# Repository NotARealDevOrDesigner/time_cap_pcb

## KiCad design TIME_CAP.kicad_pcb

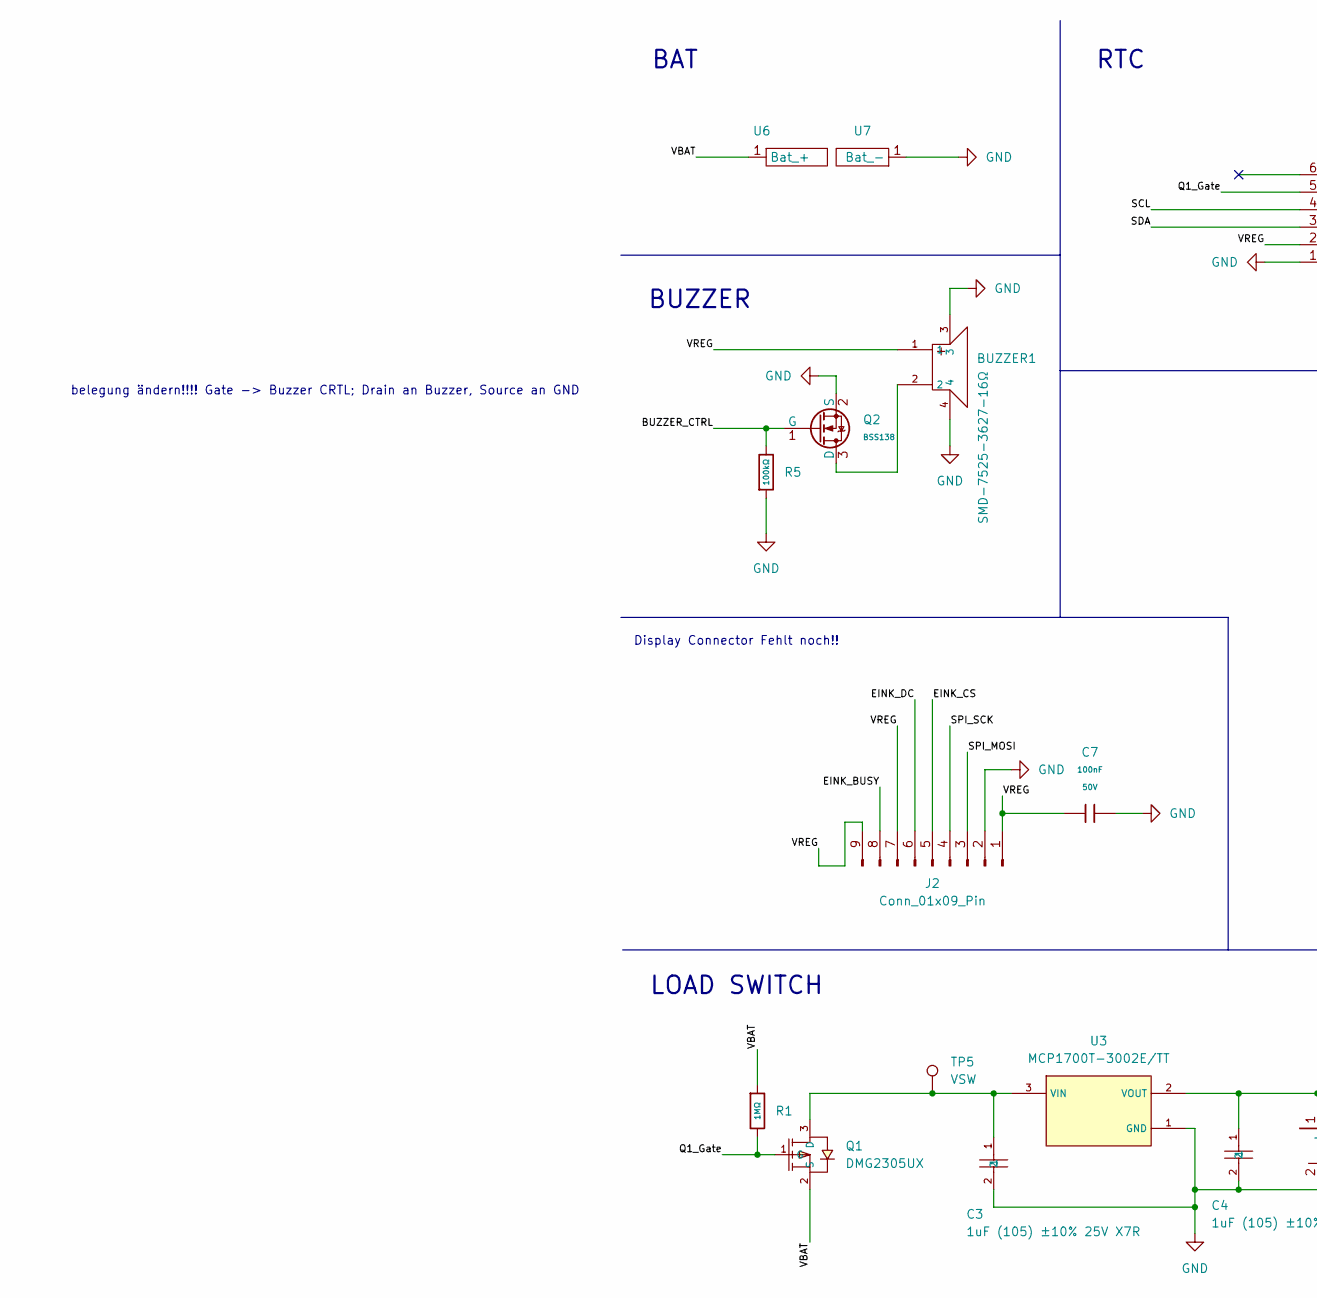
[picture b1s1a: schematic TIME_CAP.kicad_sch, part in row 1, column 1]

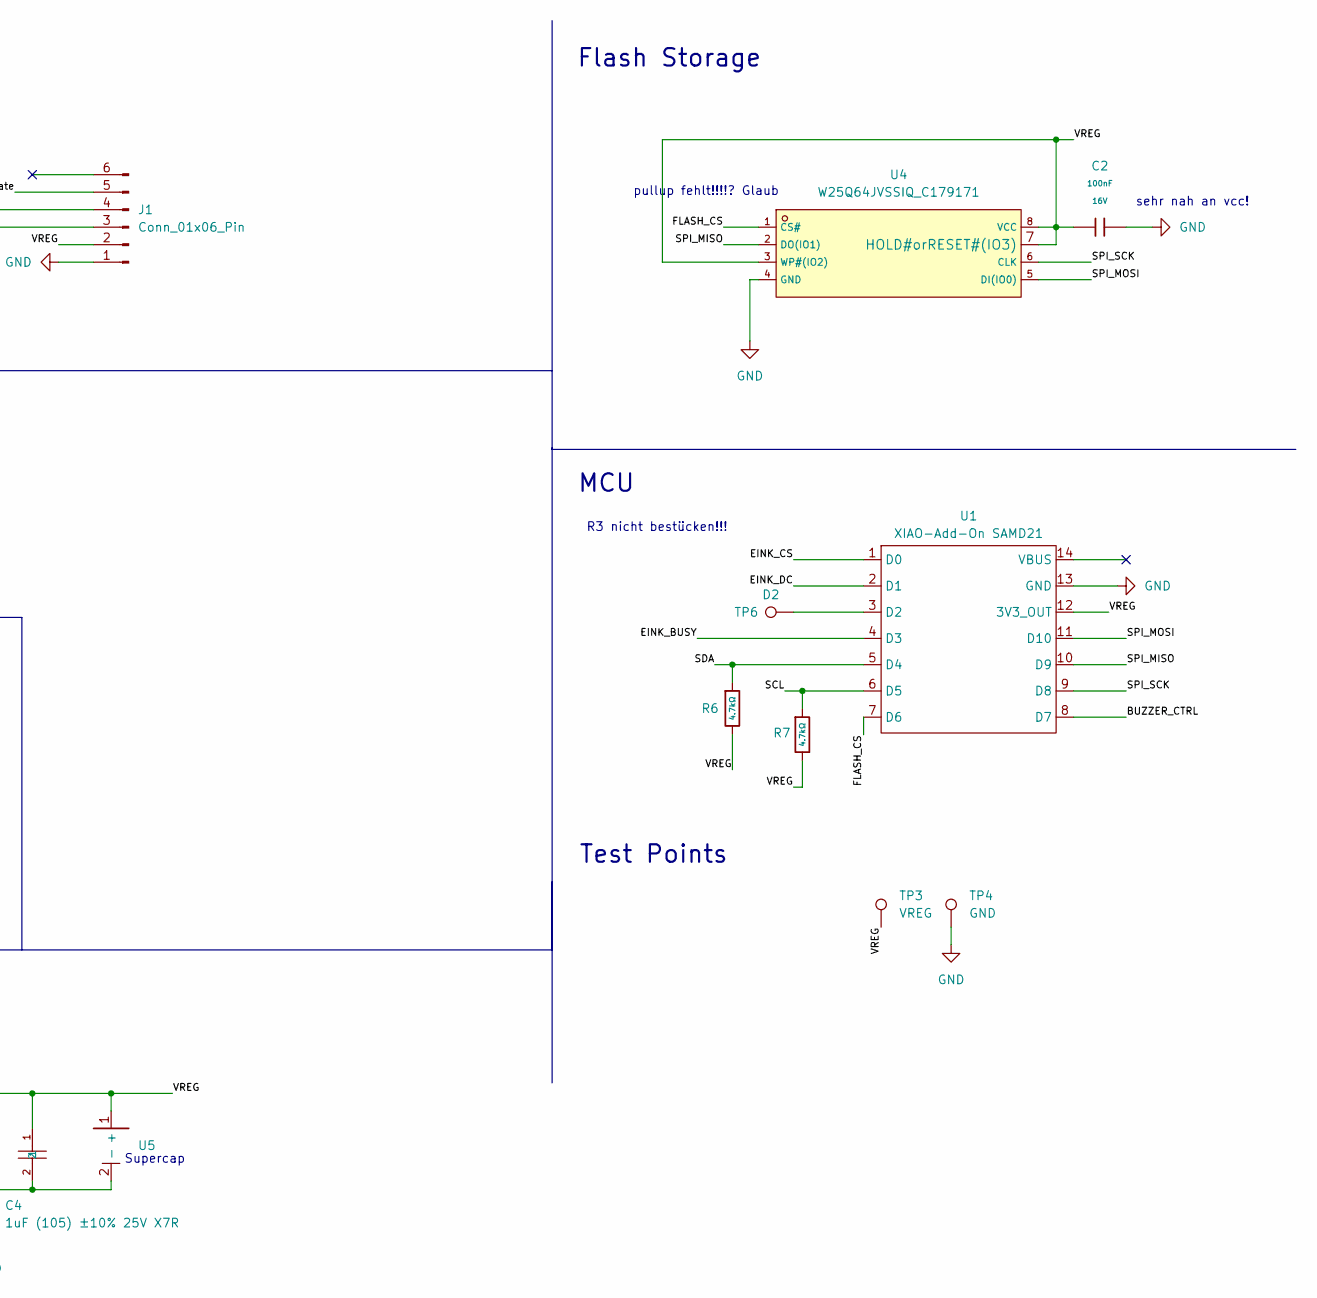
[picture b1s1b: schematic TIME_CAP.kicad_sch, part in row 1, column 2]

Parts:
BUZZER1: SMD-7525-3627-16Ω; C2685546_BUZ-SMD_4P-L7_5-W7_5-BR; LCSC C2685546
C2: 100nF; C_0402; Voltage Rated 16V; Tolerance ±10%; Part CL05B104KO5NNNC; LCSC C1525
C3, C4: 1uF (105) ±10% 25V X7R; C29936_C0603; LCSC C29936
C7: 100nF; C_0603; Voltage Rated 50V; Tolerance ±10%; Part CC0603KRX7R9BB104; LCSC C14663
J1: Conn_01x06_Pin; PinHeader_1x06_P2.54mm_Vertical_SMD_Pin1Right
J2: Conn_01x09_Pin; Display Connector
Q1: DMG2305UX; C2940629_SOT-23-3_L2_9-W1_3-P0_95-LS2_4-BR-1; LCSC C2940629
Q2: BSS138; Q_SOT-23; Part BSS138; LCSC C7420339
R1: 1MΩ; R_0603; Overload Voltage (Max) 75V; Tolerance ±1%; Part 0603WAF1004T5E; LCSC C22935
R5: 100kΩ; R_0603; Overload Voltage (Max) 75V; Tolerance ±1%; Part 0603WAF1003T5E; LCSC C25803
R6, R7: 4.7kΩ; R_0603; Overload Voltage (Max) 75V; Tolerance ±1%; Part 0603WAF4701T5E; LCSC C23162
TP3: VREG; TestPoint_Pad_D2.0mm
TP4: GND; TestPoint_Pad_D2.0mm
TP5: VSW; TestPoint_Pad_D2.0mm
TP6: D2; TestPoint_Pad_D2.0mm
U1: XIAO-Add-On SAMD21; XIAO-SAMD21-SMD
U3: MCP1700T-3002E/TT; C62244_SOT-23-3_L2_9-W1_3-P1_90-LS2_4-BR; LCSC C62244
U4: W25Q64JVSSIQ_C179171; C179171_SOIC-8_L5_3-W5_3-P1_27-LS8_0-BL; LCSC C179171
U5: FCS0V474ZFTBR24
U6, U7: Single Pad

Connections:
/BUZZER_CTRL: Q2.1 (G), R5.2, U1.8 (D7)
/EINK_BUSY: J2.8, U1.4 (D3)
/EINK_CS: J2.5, U1.1 (D0)
/EINK_DC: J2.6, U1.2 (D1)
/FLASH_CS: U1.7 (D6), U4.1 (CS#)
/Q1_Gate: J1.5, Q1.1 (G), R1.2
/SCL: J1.4, R7.1, U1.6 (D5)
/SDA: J1.3, R6.1, U1.5 (D4)
/SPI_MISO: U1.10 (D9), U4.2 (DO(IO1))
/SPI_MOSI: J2.3, U1.11 (D10), U4.5 (DI(IO0))
/SPI_SCK: J2.4, U1.9 (D8), U4.6 (CLK)
/VBAT: Q1.2 (S), R1.1, U6.1 (Bat_+_1)
/VREG: BUZZER1.1, C2.1, C4.1, C7.1, J1.2, J2.1, J2.7, J2.9, R6.2, R7.2, TP3.1 (1_1), U1.12 (3V3_OUT), U3.2 (VOUT), U4.3 (WP#(IO2)), U4.7 (HOLD#orRESET#(IO3)), U4.8 (VCC), U5.1 (+)
GND: BUZZER1.3, BUZZER1.4, C2.2, C3.2, C4.2, C7.2, J1.1, J2.2, Q2.2 (S), R5.1, TP4.1 (1_1), U1.13 (GND), U3.1 (GND), U4.4 (GND), U5.2 (-), U7.1 (Bat_-_1)
unnamed: C3.1, Q1.3 (D), TP5.1 (1_1), U3.3 (VIN)
unnamed: BUZZER1.2, Q2.3 (D)
unnamed: TP6.1 (1_1), U1.3 (D2)

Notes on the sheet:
Test Points
sehr nah an vcc!
Display Connector Fehlt noch!!
Flash Storage
MCU
LOAD SWITCH
belegung ändern!!!! Gate -> Buzzer CRTL; Drain an Buzzer, Source an GND
pullup fehlt!!!!? Glaub
BUZZER
RTC
BAT
R3 nicht bestücken!!!
Supercap

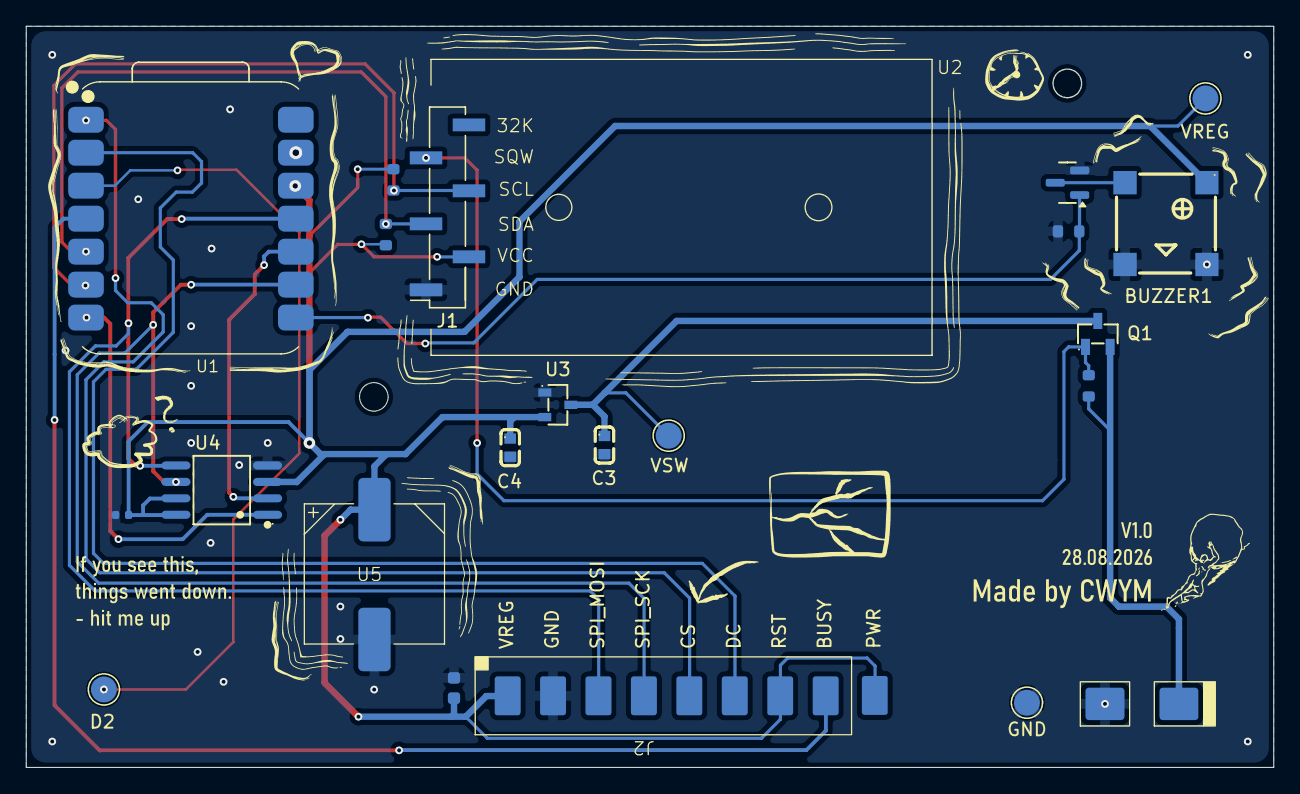
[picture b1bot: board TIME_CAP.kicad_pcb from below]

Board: 2 copper layers, 96.1 x 57.1 mm, 24 parts (24 on the bottom side), 17 nets.

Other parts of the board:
U2: DS3231 Breakout
